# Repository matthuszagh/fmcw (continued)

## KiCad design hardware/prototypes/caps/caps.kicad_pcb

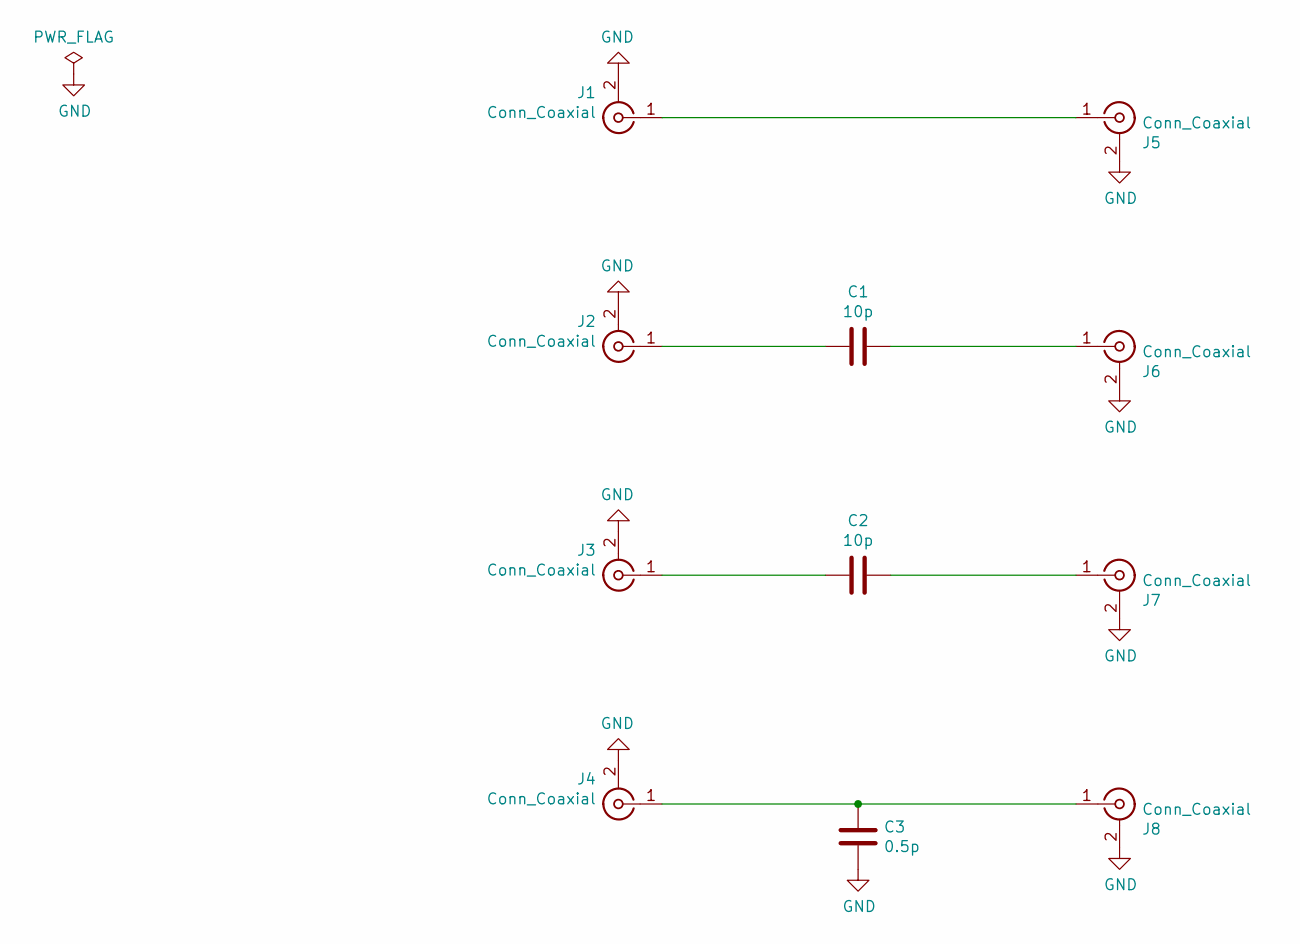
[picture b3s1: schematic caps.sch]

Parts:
C1: 10p; RF_C_0201_0603Metric
C2: 10p; RF_C_0402_1005Metric
C3: 0.5p; RF_C_0201_0603Metric
J1, J2, J3, J4, J5, J6, J7, J8: Conn_Coaxial; SMA_901-10512

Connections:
GND: C3.1, J1.2 (Ext), J2.2 (Ext), J3.2 (Ext), J4.2 (Ext), J5.2 (Ext), J6.2 (Ext), J7.2 (Ext), J8.2 (Ext)
unnamed: C1.1, J2.1 (In)
unnamed: C1.2, J6.1 (In)
unnamed: C2.1, J3.1 (In)
unnamed: C2.2, J7.1 (In)
unnamed: C3.2, J4.1 (In), J8.1 (In)
unnamed: J1.1 (In), J5.1 (In)

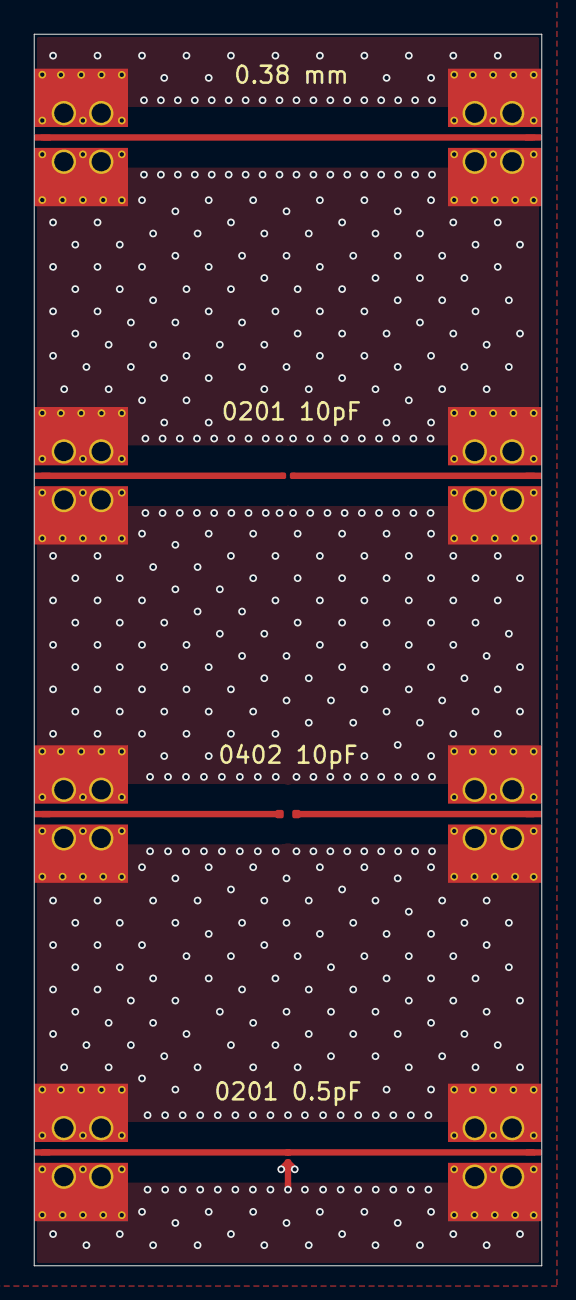
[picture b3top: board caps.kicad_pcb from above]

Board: 4 copper layers, 30.0 x 72.8 mm, 11 parts (0 on the bottom side), 7 nets.

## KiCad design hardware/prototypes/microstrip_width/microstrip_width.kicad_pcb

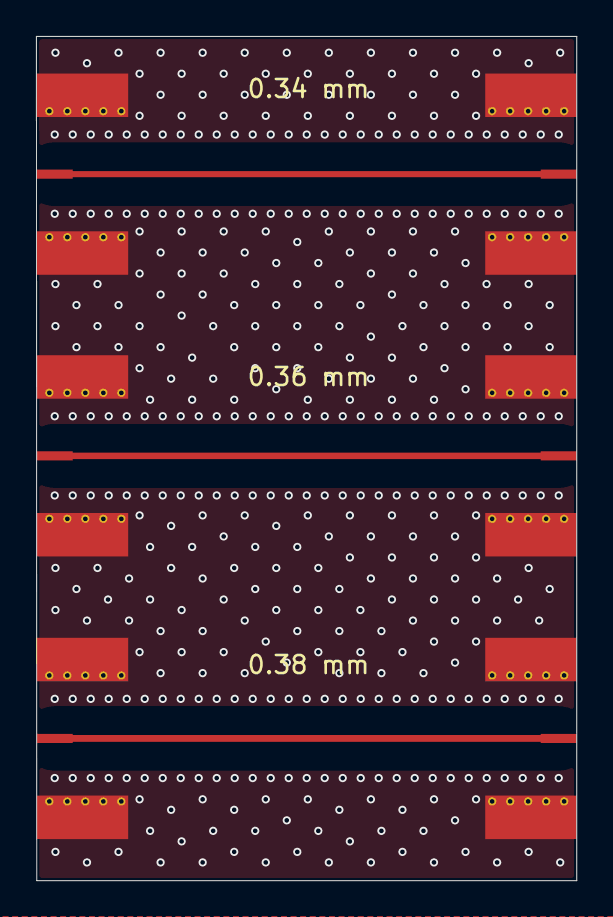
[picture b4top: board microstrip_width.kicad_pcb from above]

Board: 4 copper layers, 30.0 x 46.9 mm, 6 parts (0 on the bottom side), 4 nets.

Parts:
J1, J2, J3, J4, J5, J6: Conn_Coaxial; BU-1420701851_SMA

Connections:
GND: J1.2, J2.2, J3.2, J4.2, J5.2, J6.2
unnamed: J1.1, J4.1
unnamed: J2.1, J5.1
unnamed: J3.1, J6.1

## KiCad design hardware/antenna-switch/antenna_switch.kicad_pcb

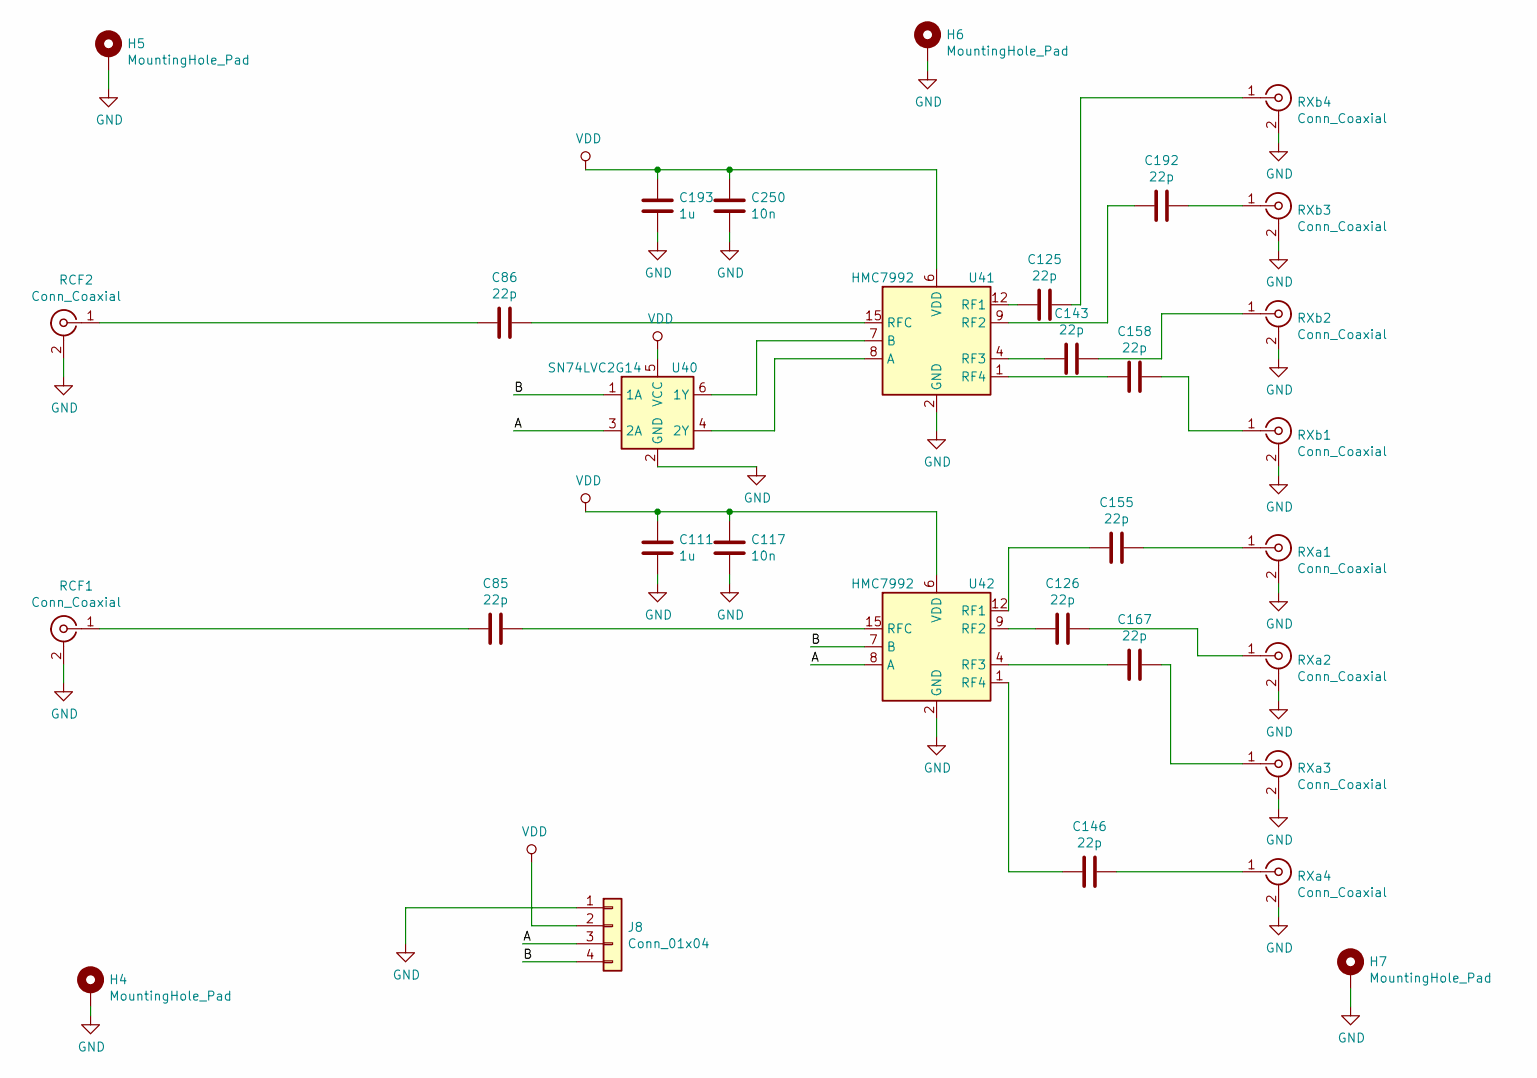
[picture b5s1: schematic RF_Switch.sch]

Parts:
C85, C86, C125, C126, C143, C146, C155, C158, C167, C192: 22p; C_0402_1005Metric
C111, C193: 1u; C_0603_1608Metric
C117, C250: 10n; C_0402_1005Metric
H4, H5, H6, H7: MountingHole_Pad; MountingHole_2.5mm_Pad_Via
J8: Conn_01x04; PinHeader_1x04_P2.54mm_Vertical
RCF1, RCF2: Conn_Coaxial; CONSMA003.062
RXa1, RXa2, RXa3, RXa4: Conn_Coaxial; CONSMA003.062
RXb1, RXb2, RXb3, RXb4: Conn_Coaxial; CONSMA003.062
U40: SN74LVC2G14; SOT-23-6
U41, U42: HMC7992; LFCSP-16-1EP_3x3mm_P0.5mm_EP1.7x1.7mm

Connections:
/RF Switch/A: J8.3, U40.3 (2A), U42.8 (A)
/RF Switch/B: J8.4, U40.1 (1A), U42.7 (B)
GND: C111.1, C117.1, C193.1, C250.1, H4.1, H5.1, H6.1, H7.1, J8.1, RCF1.2 (Ext), RCF2.2 (Ext), RXa1.2 (Ext), RXa2.2 (Ext), RXa3.2 (Ext), RXa4.2 (Ext), RXb1.2 (Ext), RXb2.2 (Ext), RXb3.2 (Ext), RXb4.2 (Ext), U40.2 (GND), U41.2 (GND), U41.3 (GND), U41.5 (GND), U41.10 (GND), U41.11 (GND), U41.13 (GND), U41.14 (GND), U41.16 (GND), U41.17 (GND), U42.2 (GND), U42.3 (GND), U42.5 (GND), U42.10 (GND), U42.11 (GND), U42.13 (GND), U42.14 (GND), U42.16 (GND), U42.17 (GND)
unnamed: C85.1, U42.15 (RFC)
unnamed: C85.2, RCF1.1 (In)
unnamed: C86.1, U41.15 (RFC)
unnamed: C86.2, RCF2.1 (In)
unnamed: C125.1, RXb4.1 (In)
unnamed: C125.2, U41.12 (RF1)
unnamed: C126.1, RXa2.1 (In)
unnamed: C126.2, U42.9 (RF2)
unnamed: C143.1, RXb2.1 (In)
unnamed: C143.2, U41.4 (RF3)
unnamed: C146.1, RXa4.1 (In)
unnamed: C146.2, U42.1 (RF4)
unnamed: C155.1, RXa1.1 (In)
unnamed: C155.2, U42.12 (RF1)
unnamed: C158.1, RXb1.1 (In)
unnamed: C158.2, U41.1 (RF4)
unnamed: C167.1, RXa3.1 (In)
unnamed: C167.2, U42.4 (RF3)
unnamed: C192.1, RXb3.1 (In)
unnamed: C192.2, U41.9 (RF2)
unnamed: U40.4 (2Y), U41.8 (A)
unnamed: U40.6 (1Y), U41.7 (B)
VDD: C111.2, C117.2, C193.2, C250.2, J8.2, U40.5 (VCC), U41.6 (VDD), U42.6 (VDD)

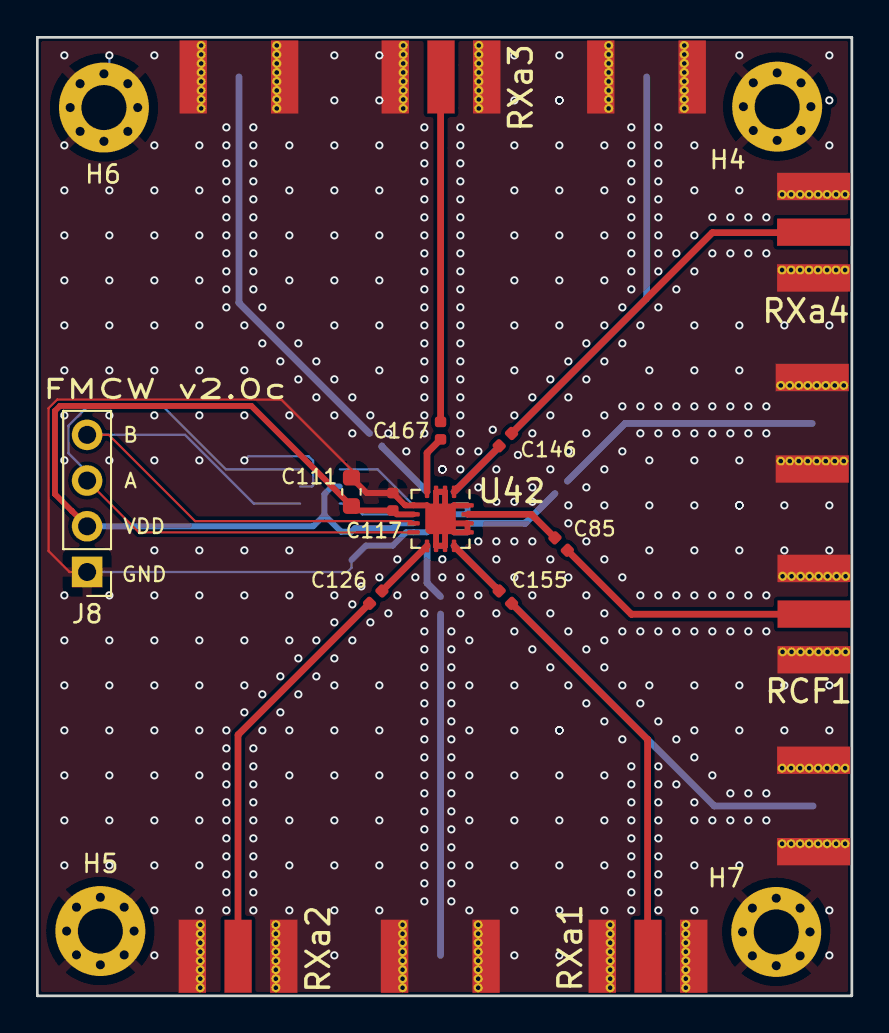
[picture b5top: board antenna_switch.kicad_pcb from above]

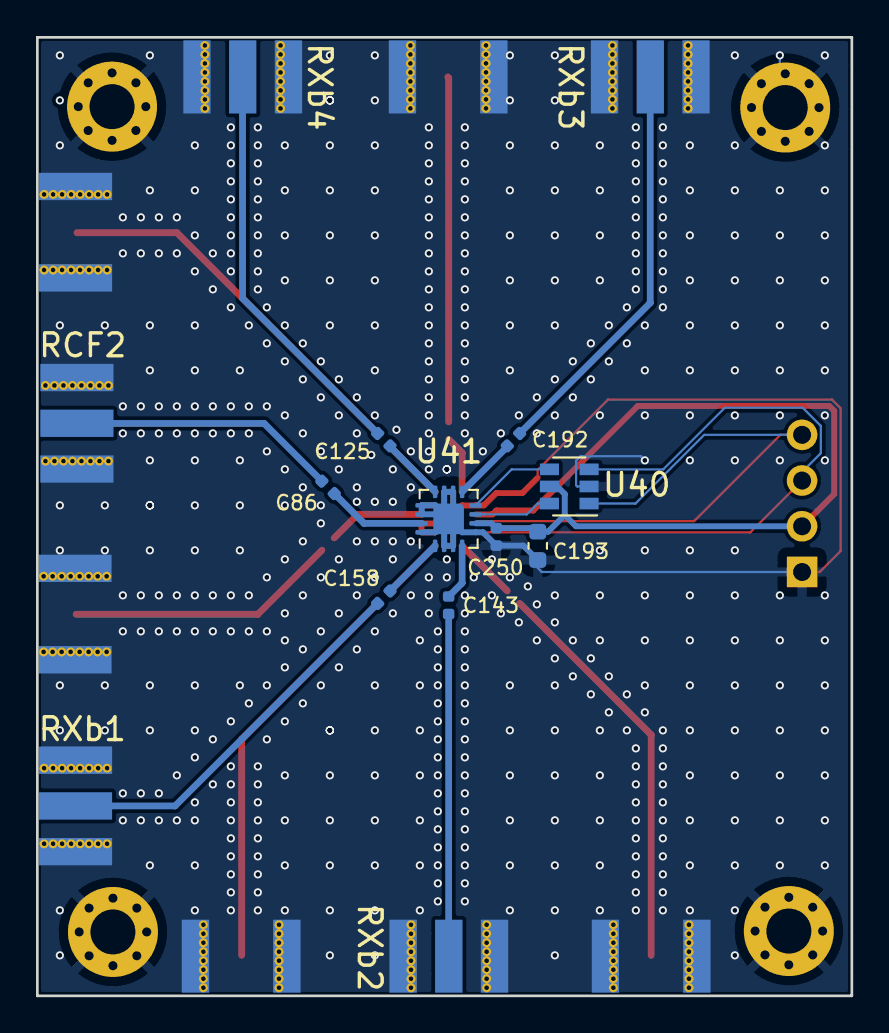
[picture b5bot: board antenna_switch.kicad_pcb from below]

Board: 4 copper layers, 45.2 x 53.3 mm, 32 parts (14 on the bottom side), 26 nets.

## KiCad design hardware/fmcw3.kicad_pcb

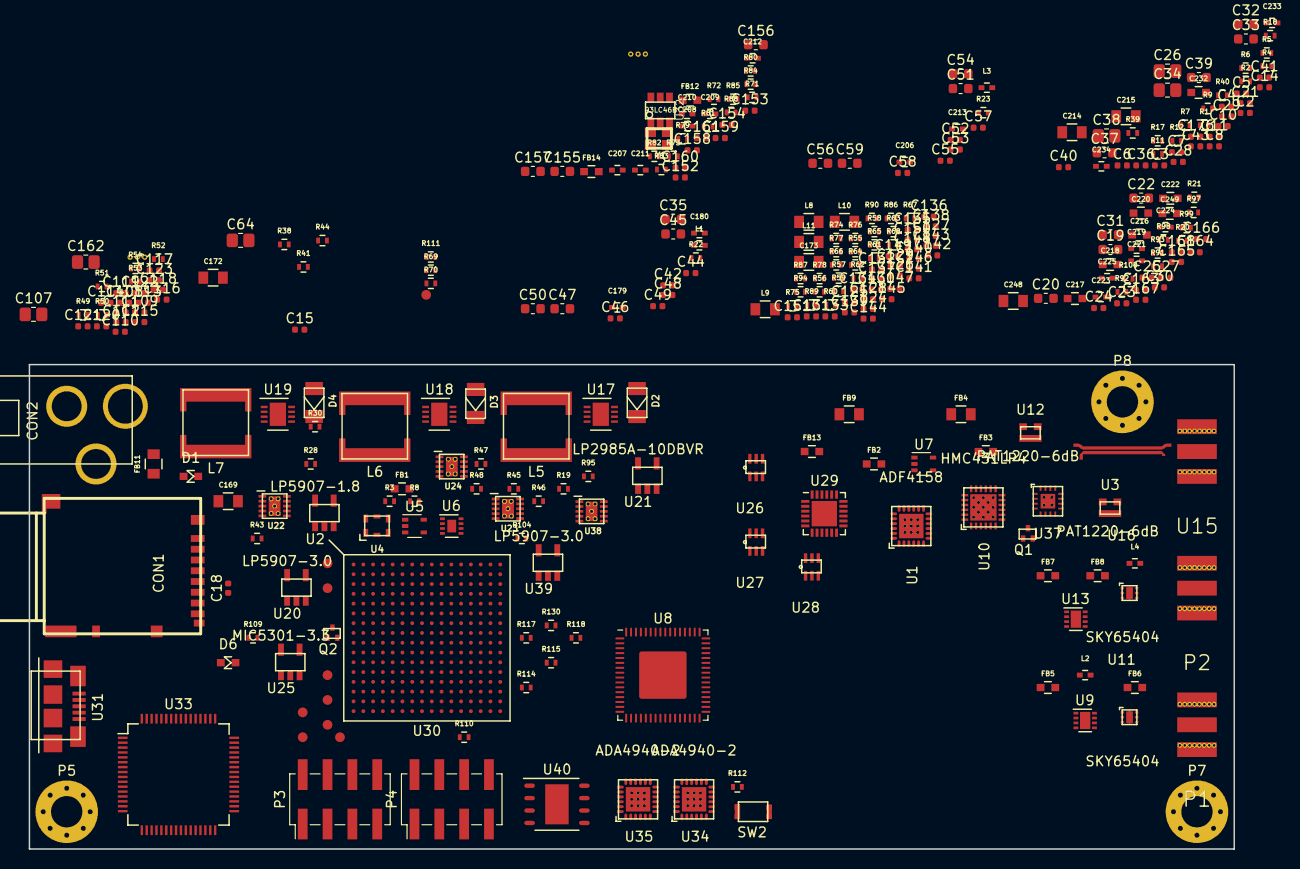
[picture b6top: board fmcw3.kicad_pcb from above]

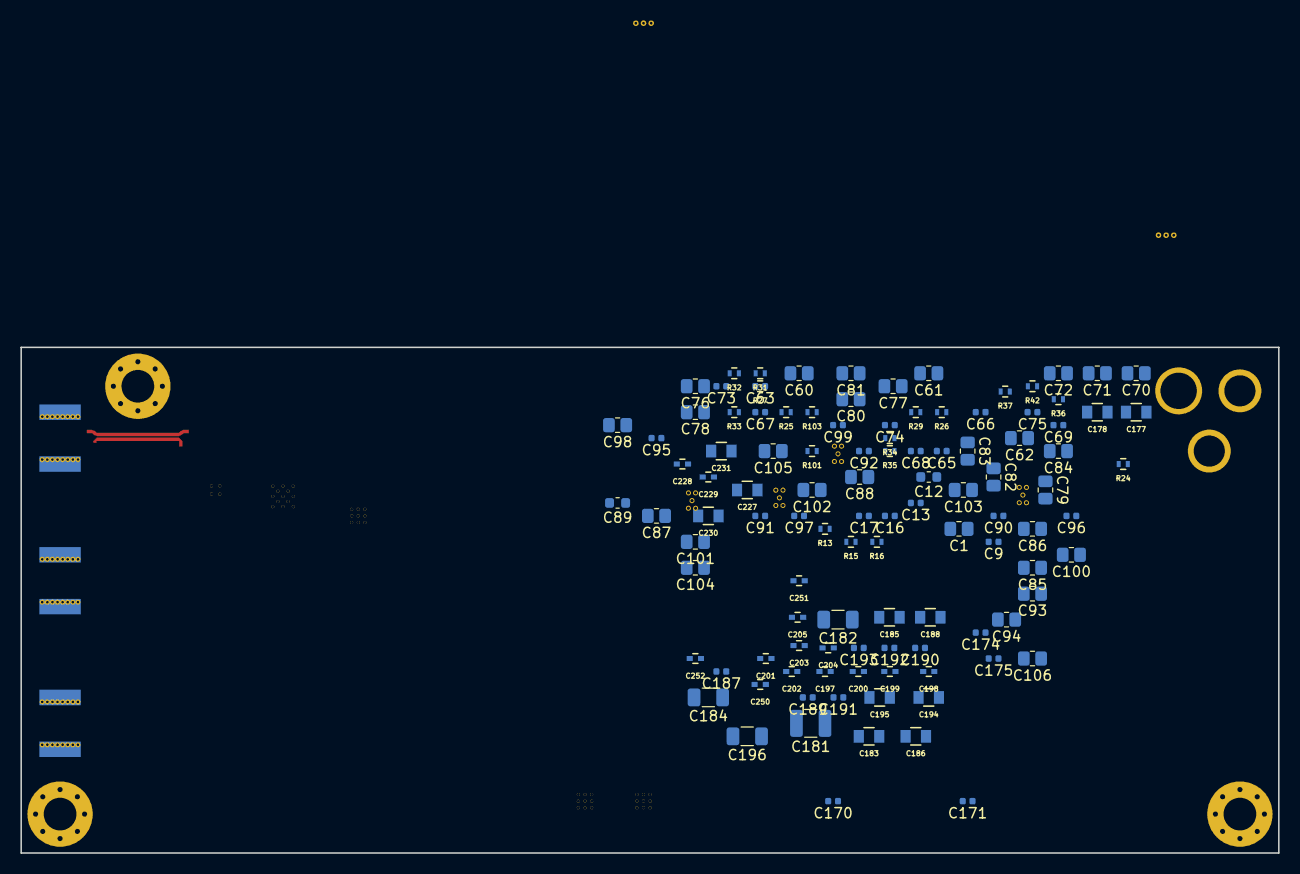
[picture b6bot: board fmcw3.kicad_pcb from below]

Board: 4 copper layers, 123.2 x 49.5 mm, 439 parts (109 on the bottom side), 271 nets, no tracks yet.

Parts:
C1, C71, C72, C81, C103, C104, C105, C107: DNP; C_0805_2012Metric
C2, C4, C6, C9, C15, C17, C18, C21, C23, C24, C25, C27, C30, C43, C49, C58, C90, C91, C92, C108, C115, C116, C120, C121, C122, C123, C132, C133, C138, C139, C150, C151, C152, C153, C154, C158, C159, C160, C161, C176: 100n; C_0402_1005Metric
C3, C5, C7, C8, C11, C36, C44, C53, C109, C110, C111, C112, C113, C114, C134, C135, C136, C137: 10p; C_0402_1005Metric
C10, C126, C127: 2.2n; C_0402_1005Metric
C12, C19, C20, C89: 1u; C_0603_1608Metric
C13, C16, C28, C63, C65, C66, C95, C96, C97, C99, C128, C129, C130, C131: 10n; C_0402_1005Metric
C14: 51p; C_0402_1005Metric
C22, C31, C39: 2.2u; C_0603_1608Metric
C26, C34, C38, C60, C61, C62, C64, C70, C76, C77, C78, C79, C80, C82, C83, C84, C85, C86, C87, C88, C93, C94, C98, C100, C101, C102, C106, C162: 10u; C_0805_2012Metric
C29, C69: 68p; C_0402_1005Metric
C32, C33, C35, C37, C45, C47, C50, C51, C54, C56, C59: DNP; C_0603_1608Metric
C40, C41, C68, C117, C118, C119, C163, C164, C165, C166, C167, C168: 100p; C_0402_1005Metric
C42, C46, C52, C55: 18p; C_0402_1005Metric
C48, C57: 0.5p; C_0402_1005Metric
C67: 39p; C_0402_1005Metric
C73: 15n; C_0402_1005Metric
C74: 8.2n; C_0402_1005Metric
C75: 4.7n; C_0402_1005Metric
C124, C125, C140, C141, C142, C143, C144, C145, C146, C147, C148, C149, C174, C175: DNP; C_0402_1005Metric
C155, C156, C157: 4.7u; C_0603_1608Metric
C169, C172, C173, C177, C178, C214, C215, C231: DNP; C_0805b
C170, C171, C187, C189, C190, C191, C192, C193: 470n; C_0402_1005Metric
C179, C206, C229: 10n; C_0402b
C180, C213, C233, C234: 100p; C_0402b
C181: 100u; C_1210_3225Metric
C182, C184, C196: 47u; C_1206_3216Metric
C183, C185, C186, C188, C194, C195: 4.7u; C_0805b
C197, C198, C199, C200, C201, C202, C203, C204, C205, C250, C251: 470n; C_0402b
C207, C210, C211, C212, C219, C221, C223, C224, C225, C228, C252: 100n; C_0402b
C208, C209: 15p; C_0402b
C216, C220, C232: 2.2u; C_0603b
C217, C218, C222, C249: 1u; C_0603b
C227, C230, C248: 10u; C_0805b
CON1: SD_Card_DM3BT; DM3BT-DSF-PEJS
CON2: BARREL_JACK; EJ508A
D1, D6: LED; LED_0603
D2, D3, D4: SS13FL; SOD-123F
F1, F2: Via; RF_via
FB1, FB2, FB3, FB5, FB6, FB7, FB8, FB12, FB13, FB14: BLM18PG181SN1D; C_0603b
FB4, FB9, FB11: CIC21P101NE; C_0805b
L1, L3: LQW15AN9N9J80D; C_0402b
L2, L4: 0.6n; C_0402b
L5, L6, L7: 33u (SRR6040A-330M); SRR6040A
L8, L9, L10, L11: 2.2u; C_0805b
P1, P2: SMA; CONSMA003.062
P3, P4: CONN_02X04; PinHeader_2x04_P2.54mm_Vertical_SMD
P5, P7, P8: CONN_01X01; MountingHole_3.2mm_M3_Pad_Via_mod
P6, P9, P10, P11, P12, P13, P14, P15, P16: CONN_01X01; TP_1.00
Q1: RE1C002UN; SOT-416
Q2: DNP(RE1C002UN); SOT-416
R1: 5.49k; R_0402b
R2, R31, R40, R50, R63, R64, R65, R66, R67, R68, R69, R74, R75, R76, R77, R78, R86, R92, R101, R110: DNP; R_0402b
R3, R8: 470k; R_0402b
R4: 3.1k; R_0402b
R5, R6, R7, R18, R82, R112, R117, R118: 4.7k; R_0402b
R9, R11, R12: 18; R_0402b
R13, R15, R16, R38, R84, R85, R88, R130: 33; R_0402b
R17, R51, R52, R53, R54, R97, R98, R99, R100: 49.9; R_0402b
R19, R29: 6.8k; R_0402b
R20, R70, R80, R81, R87, R89, R90, R91, R93, R94, R103, R114, R115: 0; R_0402b
R21: 22; R_0402b
R22, R23, R42: 100; R_0402b
R24, R109: 240; R_0402b
R25, R26, R104: 68k; R_0402b
R27: 15k; R_0402b
R28: 59k; R_0402b
R30, R59, R60, R61, R62: 8.2k; R_0402b
R32, R34, R36: 4.99k; R_0402b
R33: 7.5k; R_0402b
R35, R72, R111: 1k; R_0402b
R37: 590; R_0402b
R39: 47k; R_0402b
R41: 56; R_0402b
R43: 10.5k; R_0402b
R44, R49: 2k; R_0402b
R45: 1.87k; R_0402b
R46: 1.5k; R_0402b
R47: 3.57k; R_0402b
R48: 1.15k; R_0402b
R55, R56, R57, R58: 550; R_0402b
R71: 12k; R_0402b
R73, R83: 10k; R_0402b
R79: 2.2k; R_0402b
R95: 1.47k; R_0402b
SW2: SW_PUSH; EVP-AWBA2A
U1: ADF4158; VFQFN-24
U2: LP5907-1.8; SOT-23-5
U3, U12: PAT1220-6dB; PAT1220
U4: KT2520K
U5: NC7S04P5X; SOT-353_SC-70-5
U6: NB3N551; DFN-8
U7: TLV172DCK; SOT-353_SC-70-5
U8: LTC2292; QFN-64-1EP_9x9mm_P0.5mm_EP4.85x4.85mm
U9, U13: TRF37A73; DFN-8-1EP_2x2mm_Pitch0.5mm
U10: HMC431LP4; VQFN-24
U11, U16: SKY65404; XFDFN-6
U15: SMA; CONSMA003.062
U17, U18, U19: L7980; DFN-8-1EP_3x3mm_P0.5mm_EP1.66x2.38mm
U20, U39: LP5907-3.0; SOT-23-5
U21: LP2985A-10DBVR; SOT-23-5
U22, U23, U24, U38: TPS7A91; SON-10_2.5x2.5mm
U25: MIC5301-3.3; SOT-23-5
U26, U27, U28: 5400BL15B050E
U29: ADL5802; QFN-24-1EP_4x4mm_P0.5mm_EP2.6x2.6mm
U30: XC7A15T-1FTG256C; FTG256
U31: USB-MICRO; USB_MICRO
U32: 93LC46B; SOT-23-6
U33: FT2232H; LQFP-64_10x10mm_P0.5mm
U34, U35: ADA4940-2; VFQFN-24
U37: SE2567L; MGA-25203
U40: W25Q32JV; DFN-S-8-1EP_6x5mm_P1.27mm
Y1: ABM10-167-12.000MHZ-T3; ABM10
Z1: 15dB COUPLER; coupler

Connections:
/1V0: C76.1, C78.1, C181.1, C183.1, C184.1, C186.1, C187.1, C189.1, C191.1, C250.1, L5.2, R32.1, R38.1, U30.E10, U30.F7, U30.F9, U30.F11, U30.G6, U30.H9, U30.J6, U30.K9, U30.L8
/1V8: C97.1, C101.1, C104.1, C182.1, C185.1, C188.1, C190.1, C192.1, C193.1, C205.1, R45.1, U23.1, U23.2, U30.G8, U30.G10, U30.J10, U30.K11, U30.L10
/1V8_OSC: C12.1, U2.5, U4.6
/3V0: C35.1, C47.1, C51.1, C56.1, C93.1, C172.1, FB3.1, FB5.1, FB6.1, FB7.1, FB8.1, U20.5
/3V3A: C2.1, C3.1, C4.1, C5.1, C43.1, C99.1, C102.1, C105.1, C138.1, C139.1, C150.1, C151.1, C173.1, C176.1, FB4.1, R18.1, R39.1, R47.1, U1.6, U1.7, U1.8, U1.18, U1.19, U24.1, U24.2, U34.3, U34.4, U34.9, U34.10, U34.14, U34.20, U35.3, U35.4, U35.9, U35.10, U35.14, U35.20
/3V3D: C18.1, C25.1, C106.1, C158.1, C159.1, C160.1, C161.1, C170.1, C171.1, C194.1, C195.1, C196.1, C197.1, C198.1, C199.1, C200.1, C201.1, C202.1, C203.1, C204.1, C207.1, C210.1, C225.1, C251.1, C252.1, CON1.4, FB1.1, FB12.1, FB14.1, P3.2, P4.2, R69.1, R72.2, R73.1, R110.1, R111.1, R112.1, R117.1, R118.1, U8.32, U8.49, U25.5, U30.A6, U30.A16, U30.B3, U30.B13, U30.C10, U30.D7, U30.E4, U30.E7, U30.E14, U30.F1, U30.H15, U30.J2, U30.J12, U30.L6, U30.L16, U30.M3, U30.M13, U30.N10, U30.P7, U30.R4, U30.R14, U30.T1, U30.T11, U32.6, U33.20, U33.31, U33.42, U33.50, U33.56, U40.3, U40.7, U40.8
/3V6: C1.1, C9.1, C77.1, C80.1, C81.1, C85.1, C87.1, C88.1, C94.1, C248.1, L6.2, R24.1, R34.1, R41.1, R104.1, U2.1, U2.3, U20.1, U20.3, U23.6, U23.9, U23.10, U24.6, U24.7, U24.9, U24.10, U25.1, U39.1, U39.3
/4V5: C229.1, C230.1, C231.1, FB9.2, R19.1, U38.1, U38.2
/5V: C96.1, C100.1, C103.1, C107.2, C214.2, C215.2, FB2.1, FB13.1, R43.1, U22.1, U22.2
/10V: C21.1, C98.1, U7.5, U21.5
/ADC1+: R94.1, R100.2, U35.12
/ADC1-: R90.2, R98.2, U35.13
/ADC2+: R89.1, R99.2, U35.18
/ADC2-: R87.2, R97.2, U35.19
/ADC_CE: U1.13, U30.R3
/ADC_REF: R15.1, R21.2, U8.8, U8.9
/ADC_VCM1: C133.1, C148.1, C216.1, C219.1, R67.2, R68.1, U8.61, U34.17, U35.17
/ADC_VCM2: C30.1, C31.1, C132.1, C149.1, R74.2, R75.1, U8.20, U34.11, U35.11
/ADF_CLK: R130.2, U1.14
/ADF_DATA: U1.15, U30.M2
/ADF_LE: U1.16, U30.N1
/ADF_MUXOUT: Q2.1, U1.17, U30.K3
/ADF_REF: R16.1, U1.9
/ADF_TXDATA: U1.12, U30.P3
/FPGA_REF: R13.1, U30.N11
/LO: F1.1, F2.1, U3.1, U26.1
/MIX_ENBL: U29.7, U30.J4
/PA_OFF: Q1.1, R39.2, R40.1, U30.T2
/RF1: C42.2, U27.1
/RF2: C52.2, U28.1
/fpga/ADC_OE1: U8.58, U30.B2
/fpga/ADC_OE2: U8.23, U30.P1
/fpga/ADC_SHDN1: U8.59, U30.B1
/fpga/ADC_SHDN2: U8.22, U30.N2
/fpga/ADF_DONE: C174.1, Q2.3, U30.T4
/fpga/CARD_DETECT: CON1.9, U30.H16
/fpga/CCLK: P10.1, U30.E8, U40.6
/fpga/CLKOUT: U30.A15, U33.32
/fpga/D0: U8.43, U30.L2
/fpga/D1: U8.44, U30.K2
/fpga/D2: U8.45, U30.K1
/fpga/D3: U8.46, U30.J3
/fpga/D4: U8.47, U30.H1
/fpga/D5: U8.48, U30.H2
/fpga/D6: U8.51, U30.H3
/fpga/D7: U8.52, U30.G2
/fpga/D8: U8.53, U30.G1
/fpga/D9: U8.54, U30.F2
/fpga/D10: U8.55, U30.E1
/fpga/D11: U8.56, U30.E2
/fpga/EXT1_1: P4.3, U30.C11
/fpga/EXT1_2: P4.5, U30.B10
/fpga/EXT1_3: P4.7, U30.A9
/fpga/EXT1_4: P4.4, U30.C12
/fpga/EXT1_5: P4.6, U30.B9
/fpga/EXT1_6: P4.8, U30.A8
/fpga/EXT2_1: P3.3, U30.B7
/fpga/EXT2_2: P3.5, U30.A5
/fpga/EXT2_3: P3.7, U30.A4
/fpga/EXT2_4: P3.4, U30.A7
/fpga/EXT2_5: P3.6, U30.B5
/fpga/EXT2_6: P3.8, U30.A3
/fpga/FT_D0: U30.F15, U33.16
/fpga/FT_D1: U30.G16, U33.17
/fpga/FT_D2: U30.G15, U33.18
/fpga/FT_D3: U30.F14, U33.19
/fpga/FT_D4: U30.E16, U33.21
/fpga/FT_D5: U30.E15, U33.22
/fpga/FT_D6: U30.D16, U33.23
/fpga/FT_D7: U30.D15, U33.24
/fpga/FT_SUSPEND: U30.C16, U33.36
/fpga/INIT_B: R117.2, U30.K10
/fpga/LED: R109.1, U30.D1
/fpga/M0: R110.2, U30.M9
/fpga/M1: R114.1, U30.M10
/fpga/M2: R115.1, U30.M11
/fpga/OE#: U30.A12, U33.33
/fpga/OF1: U8.57, U30.C2
/fpga/OF2: U8.40, U30.M1
/fpga/PROGRAM_B: R112.2, SW2.1, U30.L9
/fpga/RD#: U30.B14, U33.28
/fpga/RXF#: U30.B16, U33.26
/fpga/SD_CLK: CON1.5, U30.N14
/fpga/SD_CMD: CON1.3, U30.P16
/fpga/SD_DAT0: CON1.7, U30.N16
/fpga/SD_DAT1: CON1.8, U30.M16
/fpga/SD_DAT2: CON1.1, U30.R16
/fpga/SD_DAT3: CON1.2, U30.R15
/fpga/SIWUA: U30.A13, U33.30
/fpga/SPI_CS: R118.2, U30.L12, U40.1
/fpga/SPI_DIN: P12.1, U30.J14, U40.2
/fpga/SPI_MOSI: P11.1, U30.J13, U40.5
/fpga/TCK: P15.1, R84.1, U30.L7
/fpga/TDI: P13.1, R88.1, U30.N7
/fpga/TDO: P16.1, U30.N8, U33.40
/fpga/TMS: P14.1, R85.1, U30.M7
/fpga/TXE#: U30.B15, U33.27
/fpga/WR: U30.A14, U33.29
/fpga/adc/3V0: C24.1, C27.1, C222.1, C223.1, C224.1, C249.1, R20.2, R91.1, R93.2, U8.7, U8.10, U8.18, U8.63, U39.5
/fpga/adc/REFHA: C217.1, C220.1, C221.1, U8.3, U8.4
/fpga/adc/REFHB: C19.1, C22.1, C23.1, U8.11, U8.12
/fpga/adc/REFLA: C218.1, C220.2, C221.2, U8.5, U8.6
/fpga/adc/REFLB: C20.1, C22.2, C23.2, U8.13, U8.14
/fpga/usb/1V8: C152.1, C153.1, C154.1, C156.1, U33.12, U33.37, U33.49, U33.64
/fpga/usb/DO: R73.2, R79.1, U32.1
/fpga/usb/EECLK: U32.4, U33.62
/fpga/usb/EECS: U32.5, U33.63
/fpga/usb/EEDATA: R79.2, U32.3, U33.61
/fpga/usb/USBDM: R80.2, U31.2
/fpga/usb/USBDP: R81.2, U31.3
/fpga/usb/USB_5V: R82.1, U31.1
/if/IF1+: C124.1, L8.1, R52.2, U29.4
/if/IF1-: C124.2, L9.1, R51.1, U29.3
/if/IF2+: C125.2, L11.1, R54.2, U29.16
/if/IF2-: C125.1, L10.1, R53.1, U29.15
/mixer/5VF: C108.2, C115.2, C116.2, C117.2, C118.2, C119.2, C120.2, C121.2, C122.2, C123.2, C162.2, FB13.2, R49.1, R51.2, R52.1, R53.2, R54.1, U29.6, U29.13, U29.24
/power/5V6: C79.1, C82.1, C83.1, C84.1, C86.1, C169.1, C227.1, L7.2, R36.1, R42.1, R101.2, U22.6, U22.7, U22.9, U22.10, U23.7, U38.6, U38.7, U38.9, U38.10
/power/12V: C60.1, C61.1, C62.1, C70.1, C71.1, C72.1, C89.1, C177.1, C178.1, FB11.2, R103.2, U17.8, U18.3, U18.8, U19.3, U19.8, U21.1, U21.3
/power/SYNC: R31.1, U18.2, U19.2
/tx/EN: C36.1, Q1.3, R18.2, U37.5
GND: C1.2, C2.2, C3.2, C4.2, C5.2, C6.2, C7.2, C8.1, C9.2, C12.2, C14.2, C15.2, C16.2, C17.2, C18.2, C19.2, C20.2, C21.2, C24.2, C25.2, C26.2, C27.2, C28.2, C29.2, C30.2, C31.2, C32.2, C33.1, C34.1, C35.2, C36.2, C37.1, C38.1, C39.1, C40.1, C41.1, C43.2, C44.2, C45.2, C47.2, C48.2, C49.2, C50.2, C51.2, C53.2, C54.2, C56.2, C57.2, C58.2, C59.2, C60.2, C61.2, C62.2, C64.2, C70.2, C71.2, C72.2, C76.2, C77.2, C78.2, C79.2, C80.2, C81.2, C82.2, C83.2, C84.2, C85.2, C86.2, C87.2, C88.2, C89.2, C90.2, C91.2, C92.2, C93.2, C94.2, C95.2, C98.2, C100.2, C101.2, C102.2, C103.2, C104.2, C105.2, C106.2, C107.1, C108.1, C115.1, C116.1, C117.1, C118.1, C119.1, C120.1, C121.1, C122.1, C123.1, C132.2, C133.2, C138.2, C139.2, C148.2, C149.2, C150.2, C151.2, C152.2, C153.2, C154.2, C155.2, C156.2, C157.2, C158.2, C159.2, C160.2, C161.2, C162.1, C163.1, C165.2, C166.1, C168.2, C169.2, C170.2, C171.2, C172.2, C173.2, C174.2, C175.2, C176.2, C177.2, C178.2, C179.2, C180.2, C181.2, C182.2, C183.2, C184.2, C185.2, C186.2, C187.2, C188.2, C189.2, C190.2, C191.2, C192.2, C193.2, C194.2, C195.2, C196.2, C197.2, C198.2, C199.2, C200.2, C201.2, C202.2, C203.2, C204.2, C205.2, C206.2, C207.2, C208.2, C209.2, C210.2, C211.2, C212.2, C213.2, C214.1, C215.1, C216.2, C217.2, C218.2, C219.2, C222.2, C223.2, C224.2, C225.2, C227.2, C228.2, C230.2, C231.2, C232.1, C233.1, C234.1, C248.2, C249.2, C250.2, C251.2, C252.2, CON1.6, CON1.10, CON1.11, CON2.2, CON2.3, D1.1, D2.2, D3.2, D4.2, D6.1, F1.2, F2.2, P1.2, P2.2, P3.1, P4.1, P5.1, P7.1, P8.1, Q1.2, Q2.2, R1.2, R4.2, R5.2, R17.1, R25.2, R26.2, R28.2, R33.2, R35.2, R37.2, R40.2, R44.2, R46.2, R48.2, R50.2, R70.2, R71.2, R83.2, R92.2, R95.2, R114.2, R115.2, SW2.2, U1.1, U1.2, U1.3, U1.10, U1.11, U1.PAD, U2.2, U3.3, U4.1, U4.3, U5.3, U6.6, U6.EP, U7.2, U8.17, U8.31, U8.50, U8.64, U8.65, U9.3, U9.4, U9.5, U9.6, U9.8, U9.9, U10.15, U10.PAD, U11.2, U11.5, U11.PAD, U12.3, U13.3, U13.4, U13.5, U13.6, U13.8, U13.9, U15.2, U16.2, U16.5, U16.PAD, U17.7, U17.9, U18.7, U18.9, U19.7, U19.9, U20.2, U21.2, U22.4, U22.11, U23.4, U23.11, U24.4, U24.11, U25.2, U26.2, U26.5, U27.2, U27.5, U28.2, U28.5, U29.1, U29.2, U29.5, U29.8, U29.11, U29.14, U29.17, U29.18, U29.21, U29.25, U30.A1, U30.A11, U30.B8, U30.C5, U30.C15, U30.D2, U30.D12, U30.E9, U30.F6, U30.F8, U30.F10, U30.F16, U30.G3, U30.G7, U30.G9, U30.G13, U30.H6, U30.H7, U30.J7, U30.J8, U30.J9, U30.J11, U30.K4, U30.K6, U30.K7, U30.K8, U30.K14, U30.L1, U30.L11, U30.M8, U30.N5, U30.N15, U30.P2, U30.P12, U30.R9, U30.T6, U30.T16, U31.5, U32.2, U33.1, U33.5, U33.10, U33.11, U33.13, U33.15, U33.25, U33.35, U33.47, U33.51, U34.15, U34.16, U34.21, U34.22, U34.PAD, U35.15, U35.16, U35.21, U35.22, U35.PAD, U37.1, U37.3, U37.7, U37.10, U37.12, U37.14, U38.4, U38.11, U39.2, U40.4, U40.9
unnamed: C6.1, C7.1, FB2.2, U1.22
unnamed: C8.2, U1.4
unnamed: C10.1, C14.1, U1.24, U7.1
unnamed: C10.2, R2.1, R4.1
unnamed: C11.1, R12.2
unnamed: C11.2, U1.5
unnamed: C13.1, R3.2, U5.2
unnamed: C13.2, U4.4
unnamed: C15.1, C17.1, FB1.2, U5.5, U6.7, U6.8
unnamed: C16.1, R3.1, R8.2
unnamed: C26.1, C28.1, FB3.2, U10.20
unnamed: C29.1, R7.1, U10.22
unnamed: C32.1, U37.8
unnamed: C37.2, C38.2, C39.2, C40.2, C41.2, FB4.2, U37.4, U37.16
unnamed: C42.1, L1.1, U9.7
unnamed: C46.1, U11.4
unnamed: C46.2, U9.2
unnamed: C48.1, P1.1, U11.3
unnamed: C49.1, C50.1, FB6.2, L2.2, R22.2
unnamed: C52.1, L3.1, U13.7
unnamed: C55.1, U16.4
unnamed: C55.2, U13.2
unnamed: C57.1, P2.1, U16.3
unnamed: C58.1, C59.1, FB8.2, L4.2, R23.2
unnamed: C63.1, R27.2
unnamed: C63.2, C67.2, C73.2, R32.2, R33.1, U17.5
unnamed: C64.1, CON2.1, FB11.1
unnamed: C65.1, R29.2
unnamed: C65.2, C68.2, C74.2, R34.2, R35.1, U18.5
unnamed: C66.1, R30.2
unnamed: C66.2, C69.2, C75.2, R36.2, R37.1, U19.5
unnamed: C67.1, R27.1, U17.4
unnamed: C68.1, R29.1, U18.4
unnamed: C69.1, R30.1, U19.4
unnamed: C73.1, R38.2
unnamed: C74.1, R41.2
unnamed: C75.1, R42.2
unnamed: C90.1, U22.8
unnamed: C91.1, U23.8
unnamed: C92.1, U24.8
unnamed: C95.1, U21.4
unnamed: C96.2, R43.2, R44.1, U22.3
unnamed: C97.2, R45.2, R46.1, U23.3
unnamed: C99.2, R47.2, R48.1, U24.3
unnamed: C109.1, U29.9
unnamed: C109.2, U26.4
unnamed: C110.1, U29.10
unnamed: C110.2, U26.3
unnamed: C111.1, U29.19
unnamed: C111.2, U27.4
unnamed: C112.1, U29.20
unnamed: C112.2, U27.3
unnamed: C113.1, U29.22
unnamed: C113.2, U28.4
unnamed: C114.1, U29.23
unnamed: C114.2, U28.3
unnamed: C126.1, C128.2, L8.2
unnamed: C126.2, C129.2, L9.2
unnamed: C127.1, C130.2, L10.2
unnamed: C127.2, C131.2, L11.2
unnamed: C128.1, R55.2
unnamed: C129.1, R56.2
unnamed: C130.1, R57.2
unnamed: C131.1, R58.2
unnamed: C134.1, R60.1, U34.8
unnamed: C134.2, R56.1, R60.2, U34.7
unnamed: C135.1, R55.1, R59.1, U34.6
unnamed: C135.2, R59.2, U34.5
unnamed: C136.1, R62.1, U34.2
unnamed: C136.2, R58.1, R62.2, U34.1
unnamed: C137.1, R57.1, R61.1, U34.24
unnamed: C137.2, R61.2, U34.23
unnamed: C140.1, C144.2, R63.2
unnamed: C140.2, R87.1, U34.19
unnamed: C141.1, C145.2, R64.1
unnamed: C141.2, R89.2, U34.18
unnamed: C142.1, C146.2, R65.2
unnamed: C142.2, R90.1, U34.13
unnamed: C143.1, C147.2, R66.1
unnamed: C143.2, R94.2, U34.12
unnamed: C144.1, R67.1, R76.2, U35.24
unnamed: C145.1, R68.2, R77.2, U35.1
unnamed: C146.1, R74.1, R78.2, U35.6
unnamed: C147.1, R75.2, R86.2, U35.7
unnamed: C155.1, C211.1, FB12.2, U33.4
unnamed: C157.1, C212.1, FB14.2, U33.9
unnamed: C163.2, C164.1, R97.1, U8.1
unnamed: C164.2, C165.1, R99.1, U8.2
unnamed: C166.2, C167.1, R98.1, U8.15
unnamed: C167.2, C168.1, R100.1, U8.16
unnamed: C175.1, U25.4
unnamed: C44.1, C45.1, C179.1, C180.1, FB5.2, L1.2, U9.1
unnamed: C53.1, C54.1, C206.1, C213.1, FB7.2, L3.2, U13.1
unnamed: C208.1, U33.2, Y1.1
unnamed: C209.1, U33.3, Y1.3
unnamed: C228.1, U38.8
unnamed: C229.2, R19.2, R95.1, U38.3
unnamed: C33.2, C34.2, C232.2, C233.2, C234.2, FB9.1, U37.13, U37.15
unnamed: D1.2, R24.2
unnamed: D2.1, L5.1, U17.1
unnamed: D3.1, L6.1, U18.1
unnamed: D4.1, L7.1, U19.1
unnamed: D6.2, R109.2
unnamed: L2.1, U11.6
unnamed: L4.1, U16.6
unnamed: P6.1, U30.A2
unnamed: P9.1, R111.2, U30.H10
unnamed: R1.1, U1.23
unnamed: R2.2, U1.20
unnamed: R5.1, R6.2, U7.3
unnamed: R6.1, R7.2, U7.4
unnamed: R8.1, U5.4, U6.1
unnamed: R9.2, U10.16
unnamed: R11.1, U12.2
unnamed: R9.1, R11.2, R12.1
unnamed: R13.2, U6.2
unnamed: R15.2, U6.3
unnamed: R16.2, U6.4
unnamed: R17.2, Z1.4
unnamed: R20.1, U8.19
unnamed: R21.1, U8.21
unnamed: R22.1, U11.1
unnamed: R23.1, U16.1
unnamed: R25.1, U17.6
unnamed: R26.1, U18.6
unnamed: R28.1, U19.6
unnamed: R31.2, U17.2
unnamed: R49.2, R50.1, U29.12
unnamed: R63.1, R76.1, U35.23
unnamed: R64.2, R77.1, U35.2
unnamed: R65.1, R78.1, U35.5
unnamed: R66.2, R86.1, U35.8
unnamed: R69.2, R70.1, U30.L15
unnamed: R71.1, U33.6
unnamed: R72.1, U33.14
unnamed: R80.1, U33.7
unnamed: R81.1, U33.8
unnamed: R82.2, R83.1, U33.59
unnamed: R84.2, U33.38
unnamed: R85.2, U33.41
unnamed: R88.2, U33.39
unnamed: R91.2, R92.1, U8.60
unnamed: R93.1, U8.62
unnamed: R101.1, R103.1, U17.3
unnamed: R104.2, U23.5, U25.3
unnamed: R130.1, U30.R1
unnamed: U3.2, Z1.3
unnamed: U12.1, U37.2
unnamed: U15.1, Z1.2
unnamed: U37.11, Z1.1

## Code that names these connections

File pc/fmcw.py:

import pylibftdi as ftdi
from adf4158 import ADF4158
from queue import Queue, Empty
from threading import Thread
import datetime


class FMCW():
    """Interface to the FMCW radar."""

    def __init__(self):
        SYNCFF = 0x40  # Configures bit-bang mode for synchronous FIFO.
        SIO_RTS_CTS_HS = (0x1 << 8)
        self.device = ftdi.Device(mode='b', interface_select=ftdi.INTERFACE_A)
        self.device.open()
        self.device.ftdi_fn.ftdi_set_bitmode(0xff, SYNCFF)
        self.device.ftdi_fn.ftdi_read_data_set_chunksize(0x10000)
        self.device.ftdi_fn.ftdi_write_data_set_chunksize(0x10000)
        self.device.ftdi_fn.ftdi_setflowctrl(SIO_RTS_CTS_HS)
        self.device.flush()

        self.pll = ADF4158()
        self.fclk = 40e6
        self.fpd_freq = self.fclk/2

    def close(self):
        self.device.close()
        return

    def send_packet(self, x, cmd):
        try:
            l = len(x)
        except TypeError:
            l = 1
            x = [x]

        header = [0xaa, l, cmd]
        b = bytearray(header+x)
        # print map(hex, map(ord, str(b)))
        return self.device.write(str(b))

    def clear_gpio(self, led=False, pa_off=False, mix_enbl=False, adf_ce=False):
        w = 0
        if led:
            w |= 1 << 0
        if pa_off:
            w |= 1 << 1
        if mix_enbl:
            w |= 1 << 2
        if adf_ce:
            w |= 1 << 3
        return self.send_packet(w, 0)

    def set_gpio(self, led=False, pa_off=False, mix_enbl=False, adf_ce=False):
        w = 0
        if led:
            w |= 1 << 0
        if pa_off:
            w |= 1 << 1
        if mix_enbl:
            w |= 1 << 2
        if adf_ce:
            w |= 1 << 3
        return self.send_packet(w, 1)

    def clear_adc(self, oe1=False, oe2=False, shdn1=False, shdn2=False):
        w = 0
        if oe1:
            w |= 1 << 0
        if oe2:
            w |= 1 << 1
        if shdn1:
            w |= 1 << 2
        if shdn2:
            w |= 1 << 3
        return self.send_packet(w, 2)

    def set_adc(self, oe1=False, oe2=False, shdn1=False, shdn2=False):
        w = 0
        if oe1:
            w |= 1 << 0
        if oe2:
            w |= 1 << 1
        if shdn1:
            w |= 1 << 2
        if shdn2:
            w |= 1 << 3
        return self.send_packet(w, 3)

    def write_pll_reg(self, n):
        reg = self.pll.registers[n]
        w = [(reg & 0xff) | n, (reg >> 8) & 0xff,
             (reg >> 16) & 0xff, (reg >> 24) & 0xff]
        return self.send_packet(w, 4)

    def write_pll(self):
        self.write_pll_reg(7)
        self.pll.write_value(step_sel=0)
        self.write_pll_reg(6)
        self.pll.write_value(step_sel=1)
        self.write_pll_reg(6)
        self.pll.write_value(dev_sel=0)
        self.write_pll_reg(5)
        self.pll.write_value(dev_sel=1)
        self.write_pll_reg(5)
        for i in range(4, -1, -1):
            self.write_pll_reg(i)

    def set_sweep(self, fstart, bw, length, delay):
        real_delay = self.pll.freq_to_regs(
            fstart, self.fpd_freq, bw, length, delay)
        self.write_pll()
        return real_delay

    def write_sweep_timer(self, length):
        length = int(self.fclk*length)
        w = [(length & 0xff), (length >> 8) & 0xff,
             (length >> 16) & 0xff, (length >> 24) & 0xff]
        return self.send_packet(w, 5)

    def write_sweep_delay(self, length):
        length = int(self.fclk*length)
        w = [(length & 0xff), (length >> 8) & 0xff,
             (length >> 16) & 0xff, (length >> 24) & 0xff]
        return self.send_packet(w, 6)

    def set_channels(self, a=True, b=True):
        w = 0
        if a:
            w |= 1 << 0
        if b:
            w |= 1 << 1
        return self.send_packet(w, 7)

    def set_downsampler(self, enable=True, quarter=False):
        w = 0
        if enable:
            w |= 1 << 0
        if quarter:
            w |= 1 << 1
        return self.send_packet(w, 8)

    def write_decimate(self, decimate):
        if decimate > 2**16-1 or decimate < 1:
            raise ValueError("Invalid decimate value")
        decimate = int(decimate) - 1
        w = [decimate & 0xff, (decimate >> 8) & 0xff]
        return self.send_packet(w, 9)

    def write_pa_off_timer(self, length):
        length = int(self.fclk*length)
        w = [(length & 0xff), (length >> 8) & 0xff,
             (length >> 16) & 0xff, (length >> 24) & 0xff]
        return self.send_packet(w, 10)

    def clear_buffer(self):
        return self.send_packet(0, 11)


class Writer(Thread):
    def __init__(self, filename, queue):
        Thread.__init__(self)
        self.queue = queue
        self.f = open(filename, 'wb')

    def run(self):
        wrote = 0
        while True:
            try:
                d = self.queue.get(True, 0.5)
            except Empty:
                print('Timeout', wrote)
                self.f.close()
                return
            if len(d) == 0:
                print('Closed', wrote)
                self.f.close()
                return
            else:
                self.f.write(d)
                wrote += len(d)


if __name__ == '__main__':
    fmcw = FMCW()

    f0 = 5.3e9
    bw = 600e6
    tsweep = 1e-3
    tdelay = 2e-3
    pa_off_advance = 0.2e-3
    decimate = 3
    ch_a = True
    ch_b = True
    downsampler = True
    quarter = False

    fmcw.set_gpio(led=True, adf_ce=True)
    fmcw.set_adc(oe2=True)
    fmcw.clear_adc(oe1=True, shdn1=True, shdn2=True)
    delay = fmcw.set_sweep(f0, bw, tsweep, tdelay)

    fmcw.set_downsampler(enable=downsampler, quarter=quarter)
    fmcw.write_sweep_timer(tsweep)
    fmcw.write_sweep_delay(tdelay)
    fmcw.write_decimate(decimate)
    fmcw.write_pa_off_timer(tdelay - pa_off_advance)
    fmcw.clear_gpio(pa_off=True)
    fmcw.clear_buffer()

    q = Queue()

    date = datetime.datetime.now().strftime("%Y-%m-%d %H:%M:%S")

    settings_dict = {'date': date, 'f0': f0, 'bw': bw, 'tsweep': tsweep, 'tdelay': tdelay,
                     'a': ch_a, 'b': ch_b, 'decimate': decimate, 'downsampler': downsampler, 'quarter': quarter}

    settings = 'fmcw; {}'.format(settings_dict)

    ls = len(settings)
    len_settings = ''.join(map(chr, [ls & 0xff, (ls >> 8) & 0xff]))

    settings = len_settings+settings

    q.put(settings)

    writer = Writer('fmcw.log', q)
    writer.start()

    fmcw.set_channels(a=ch_a, b=ch_b)

    try:
        while True:
            r = fmcw.device.read(0x10000)
            if len(r) != 0:
                q.put(r)
    finally:
        fmcw.set_adc(oe1=True, shdn1=True, shdn2=True)
        fmcw.set_channels(a=False, b=False)
        fmcw.clear_gpio(led=True, adf_ce=True)
        fmcw.set_gpio(pa_off=True)
        fmcw.clear_buffer()
        fmcw.close()
        print('Done')
        q.put('')
        writer.join()
